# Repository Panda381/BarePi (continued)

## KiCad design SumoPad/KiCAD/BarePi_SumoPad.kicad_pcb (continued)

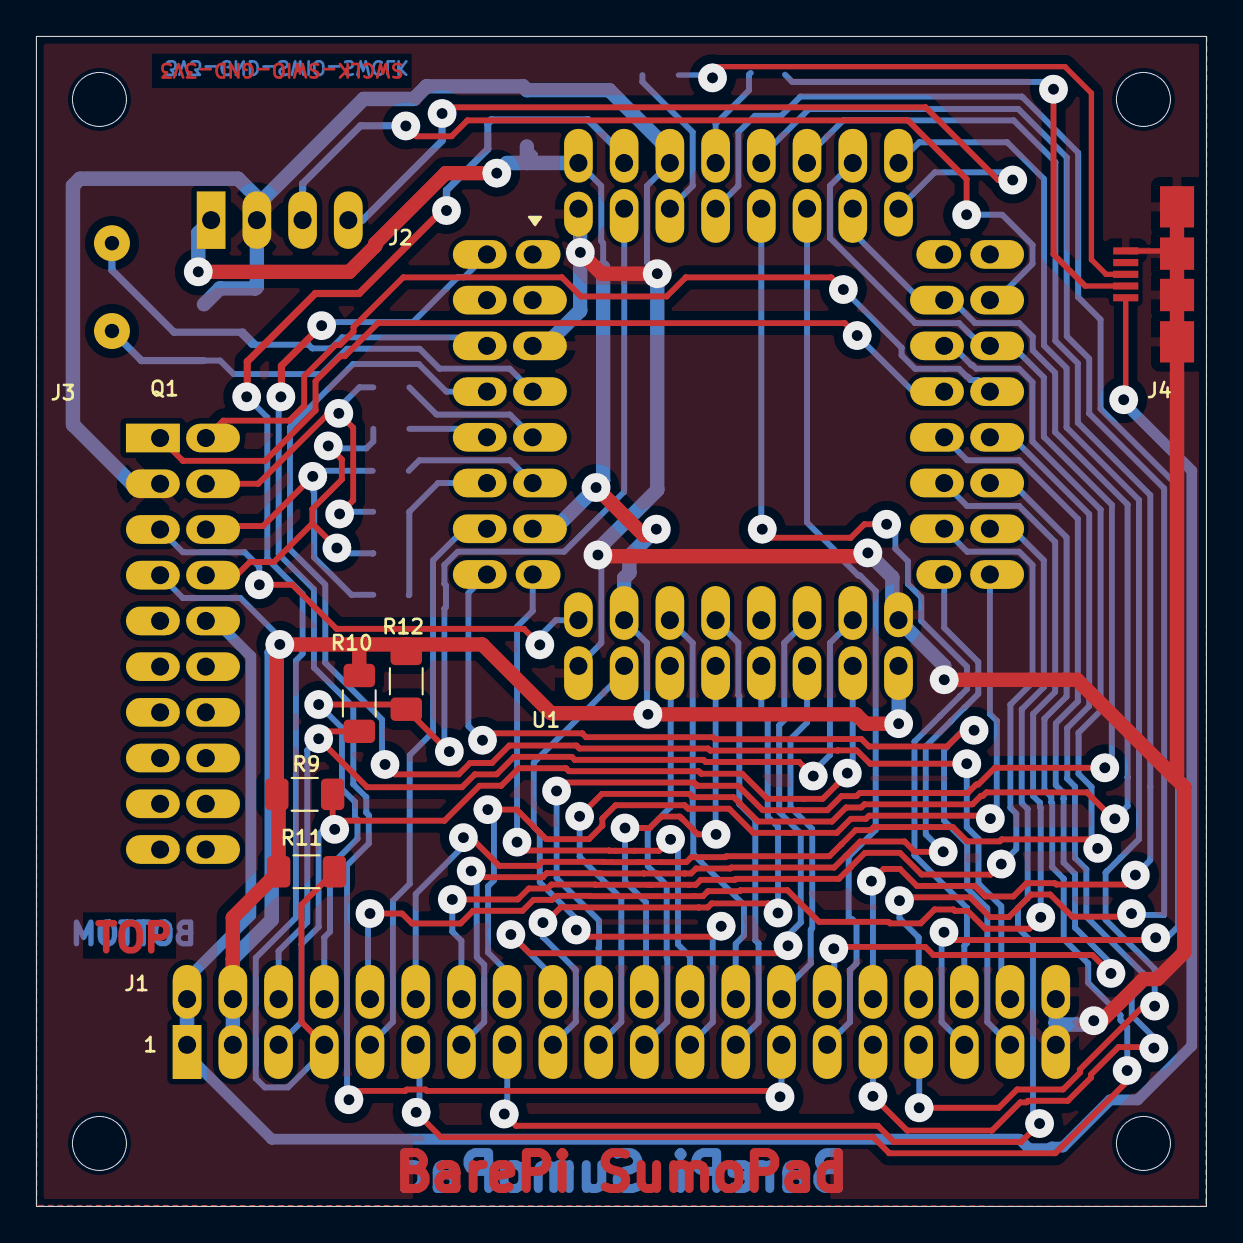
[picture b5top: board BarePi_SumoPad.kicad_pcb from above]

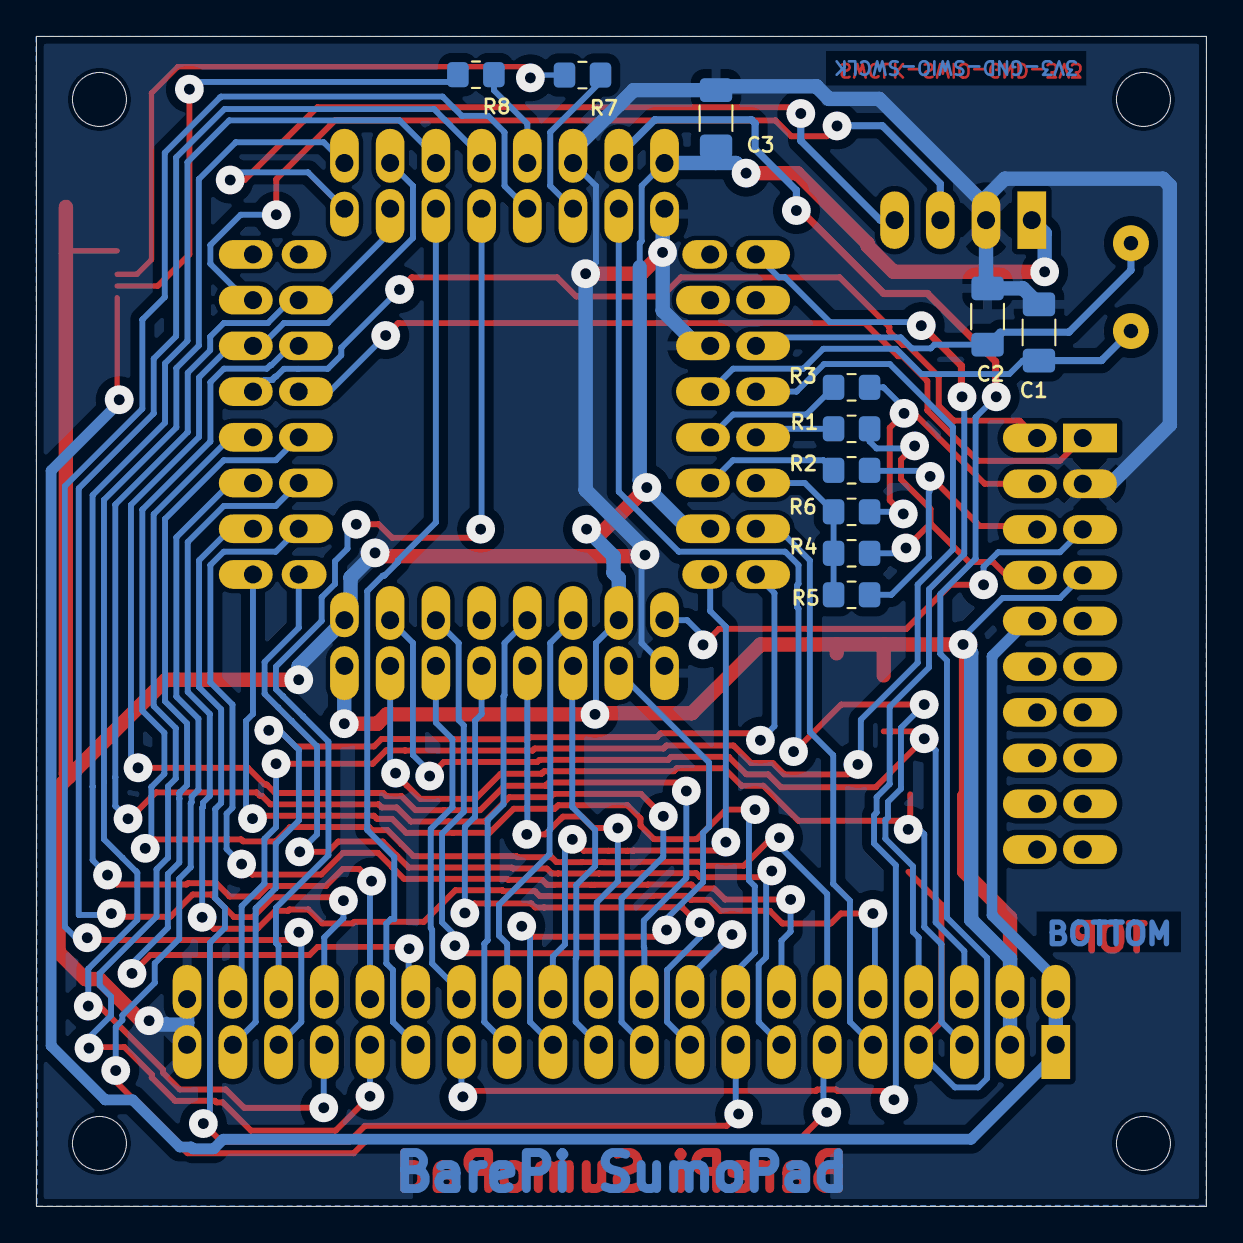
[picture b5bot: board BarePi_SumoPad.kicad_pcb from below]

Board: 2 copper layers, 65.0 x 65.0 mm, 21 parts (11 on the bottom side), 55 nets.

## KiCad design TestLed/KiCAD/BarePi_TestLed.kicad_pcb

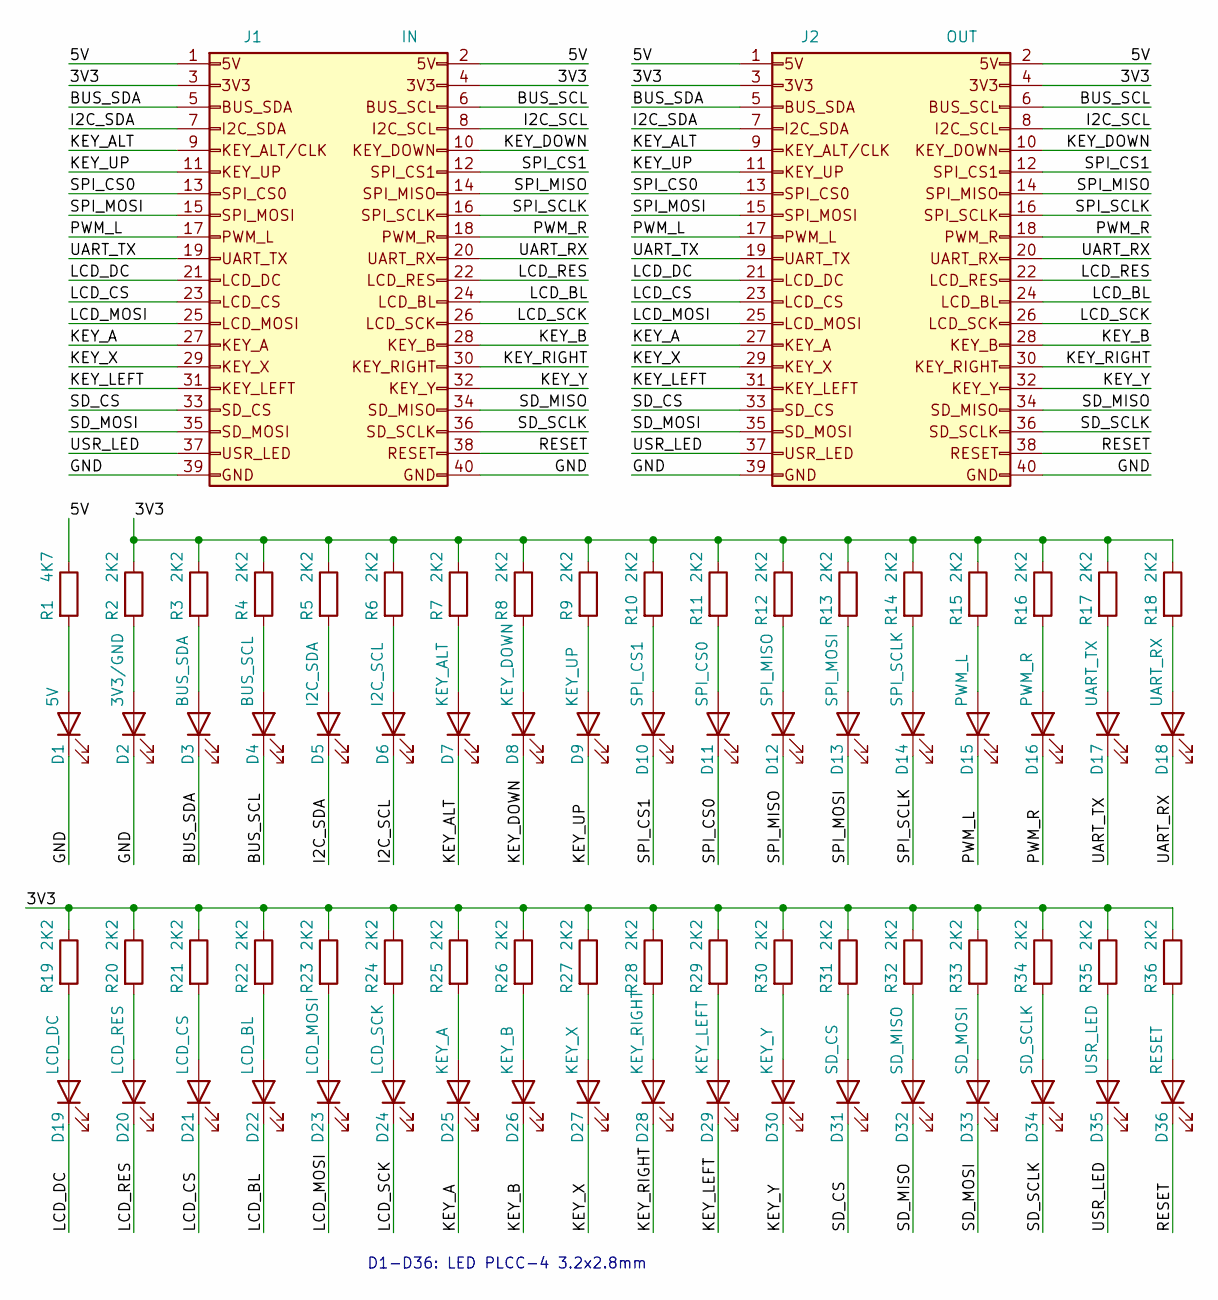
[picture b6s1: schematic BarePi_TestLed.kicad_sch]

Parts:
D1: 5V; Raspberry_LED_Avago_PLCC4_3.2x2.8mm_CW
D2: 3V3/GND; Raspberry_LED_Avago_PLCC4_3.2x2.8mm_CW
D3: BUS_SDA; Raspberry_LED_Avago_PLCC4_3.2x2.8mm_CW
D4: BUS_SCL; Raspberry_LED_Avago_PLCC4_3.2x2.8mm_CW
D5: I2C_SDA; Raspberry_LED_Avago_PLCC4_3.2x2.8mm_CW
D6: I2C_SCL; Raspberry_LED_Avago_PLCC4_3.2x2.8mm_CW
D7: KEY_ALT; Raspberry_LED_Avago_PLCC4_3.2x2.8mm_CW
D8: KEY_DOWN; Raspberry_LED_Avago_PLCC4_3.2x2.8mm_CW
D9: KEY_UP; Raspberry_LED_Avago_PLCC4_3.2x2.8mm_CW
D10: SPI_CS1; Raspberry_LED_Avago_PLCC4_3.2x2.8mm_CW
D11: SPI_CS0; Raspberry_LED_Avago_PLCC4_3.2x2.8mm_CW
D12: SPI_MISO; Raspberry_LED_Avago_PLCC4_3.2x2.8mm_CW
D13: SPI_MOSI; Raspberry_LED_Avago_PLCC4_3.2x2.8mm_CW
D14: SPI_SCLK; Raspberry_LED_Avago_PLCC4_3.2x2.8mm_CW
D15: PWM_L; Raspberry_LED_Avago_PLCC4_3.2x2.8mm_CW
D16: PWM_R; Raspberry_LED_Avago_PLCC4_3.2x2.8mm_CW
D17: UART_TX; Raspberry_LED_Avago_PLCC4_3.2x2.8mm_CW
D18: UART_RX; Raspberry_LED_Avago_PLCC4_3.2x2.8mm_CW
D19: LCD_DC; Raspberry_LED_Avago_PLCC4_3.2x2.8mm_CW
D20: LCD_RES; Raspberry_LED_Avago_PLCC4_3.2x2.8mm_CW
D21: LCD_CS; Raspberry_LED_Avago_PLCC4_3.2x2.8mm_CW
D22: LCD_BL; Raspberry_LED_Avago_PLCC4_3.2x2.8mm_CW
D23: LCD_MOSI; Raspberry_LED_Avago_PLCC4_3.2x2.8mm_CW
D24: LCD_SCK; Raspberry_LED_Avago_PLCC4_3.2x2.8mm_CW
D25: KEY_A; Raspberry_LED_Avago_PLCC4_3.2x2.8mm_CW
D26: KEY_B; Raspberry_LED_Avago_PLCC4_3.2x2.8mm_CW
D27: KEY_X; Raspberry_LED_Avago_PLCC4_3.2x2.8mm_CW
D28: KEY_RIGHT; Raspberry_LED_Avago_PLCC4_3.2x2.8mm_CW
D29: KEY_LEFT; Raspberry_LED_Avago_PLCC4_3.2x2.8mm_CW
D30: KEY_Y; Raspberry_LED_Avago_PLCC4_3.2x2.8mm_CW
D31: SD_CS; Raspberry_LED_Avago_PLCC4_3.2x2.8mm_CW
D32: SD_MISO; Raspberry_LED_Avago_PLCC4_3.2x2.8mm_CW
D33: SD_MOSI; Raspberry_LED_Avago_PLCC4_3.2x2.8mm_CW
D34: SD_SCLK; Raspberry_LED_Avago_PLCC4_3.2x2.8mm_CW
D35: USR_LED; Raspberry_LED_Avago_PLCC4_3.2x2.8mm_CW
D36: RESET; Raspberry_LED_Avago_PLCC4_3.2x2.8mm_CW
J1: IN; Raspberry_IN_PinHeader_2x20_P2.54mm_Horizontal
J2: OUT; Raspberry_OUT_PinSocket_2x20_P2.54mm_Horizontal
R1: 4K7; R_0805_2012Metric_Pad1.20x1.40mm_HandSolder
R2, R3, R4, R5, R6, R7, R8, R9, R10, R11, R12, R13, R14, R15, R16, R17, R18, R19, R20, R21, R22, R23, R24, R25, R26, R27, R28, R29, R30, R31, R32, R33, R34, R35, R36: 2K2; R_0805_2012Metric_Pad1.20x1.40mm_HandSolder

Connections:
/3V3: J1.3, J1.4, J2.3, J2.4, R2.1, R3.1, R4.1, R5.1, R6.1, R7.1, R8.1, R9.1, R10.1, R11.1, R12.1, R13.1, R14.1, R15.1, R16.1, R17.1, R18.1, R19.1, R20.1, R21.1, R22.1, R23.1, R24.1, R25.1, R26.1, R27.1, R28.1, R29.1, R30.1, R31.1, R32.1, R33.1, R34.1, R35.1, R36.1
/5V: J1.1, J1.2, J2.1, J2.2, R1.1
/BUS_SCL: D4.1 (K), J1.6, J2.6
/BUS_SDA: D3.1 (K), J1.5, J2.5
/GND: D1.1 (K), D2.1 (K), J1.39, J1.40, J2.39, J2.40
/I2C_SCL: D6.1 (K), J1.8, J2.8
/I2C_SDA: D5.1 (K), J1.7, J2.7
/KEY_A: D25.1 (K), J1.27, J2.27
/KEY_ALT: D7.1 (K), J1.9, J2.9
/KEY_B: D26.1 (K), J1.28, J2.28
/KEY_DOWN: D8.1 (K), J1.10, J2.10
/KEY_LEFT: D29.1 (K), J1.31, J2.31
/KEY_RIGHT: D28.1 (K), J1.30, J2.30
/KEY_UP: D9.1 (K), J1.11, J2.11
/KEY_X: D27.1 (K), J1.29, J2.29
/KEY_Y: D30.1 (K), J1.32, J2.32
/LCD_BL: D22.1 (K), J1.24, J2.24
/LCD_CS: D21.1 (K), J1.23, J2.23
/LCD_DC: D19.1 (K), J1.21, J2.21
/LCD_MOSI: D23.1 (K), J1.25, J2.25
/LCD_RES: D20.1 (K), J1.22, J2.22
/LCD_SCK: D24.1 (K), J1.26, J2.26
/PWM_L: D15.1 (K), J1.17, J2.17
/PWM_R: D16.1 (K), J1.18, J2.18
/RESET: D36.1 (K), J1.38, J2.38
/SD_CS: D31.1 (K), J1.33, J2.33
/SD_MISO: D32.1 (K), J1.34, J2.34
/SD_MOSI: D33.1 (K), J1.35, J2.35
/SD_SCLK: D34.1 (K), J1.36, J2.36
/SPI_CS0: D11.1 (K), J1.13, J2.13
/SPI_CS1: D10.1 (K), J1.12, J2.12
/SPI_MISO: D12.1 (K), J1.14, J2.14
/SPI_MOSI: D13.1 (K), J1.15, J2.15
/SPI_SCLK: D14.1 (K), J1.16, J2.16
/UART_RX: D18.1 (K), J1.20, J2.20
/UART_TX: D17.1 (K), J1.19, J2.19
/USR_LED: D35.1 (K), J1.37, J2.37
unnamed: D1.2 (A), R1.2
unnamed: D2.2 (A), R2.2
unnamed: D3.2 (A), R3.2
unnamed: D4.2 (A), R4.2
unnamed: D5.2 (A), R5.2
unnamed: D6.2 (A), R6.2
unnamed: D7.2 (A), R7.2
unnamed: D8.2 (A), R8.2
unnamed: D9.2 (A), R9.2
unnamed: D10.2 (A), R10.2
unnamed: D11.2 (A), R11.2
unnamed: D12.2 (A), R12.2
unnamed: D13.2 (A), R13.2
unnamed: D14.2 (A), R14.2
unnamed: D15.2 (A), R15.2
unnamed: D16.2 (A), R16.2
unnamed: D17.2 (A), R17.2
unnamed: D18.2 (A), R18.2
unnamed: D19.2 (A), R19.2
unnamed: D20.2 (A), R20.2
unnamed: D21.2 (A), R21.2
unnamed: D22.2 (A), R22.2
unnamed: D23.2 (A), R23.2
unnamed: D24.2 (A), R24.2
unnamed: D25.2 (A), R25.2
unnamed: D26.2 (A), R26.2
unnamed: D27.2 (A), R27.2
unnamed: D28.2 (A), R28.2
unnamed: D29.2 (A), R29.2
unnamed: D30.2 (A), R30.2
unnamed: D31.2 (A), R31.2
unnamed: D32.2 (A), R32.2
unnamed: D33.2 (A), R33.2
unnamed: D34.2 (A), R34.2
unnamed: D35.2 (A), R35.2
unnamed: D36.2 (A), R36.2

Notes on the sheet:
D1-D36: LED PLCC-4 3.2x2.8mm

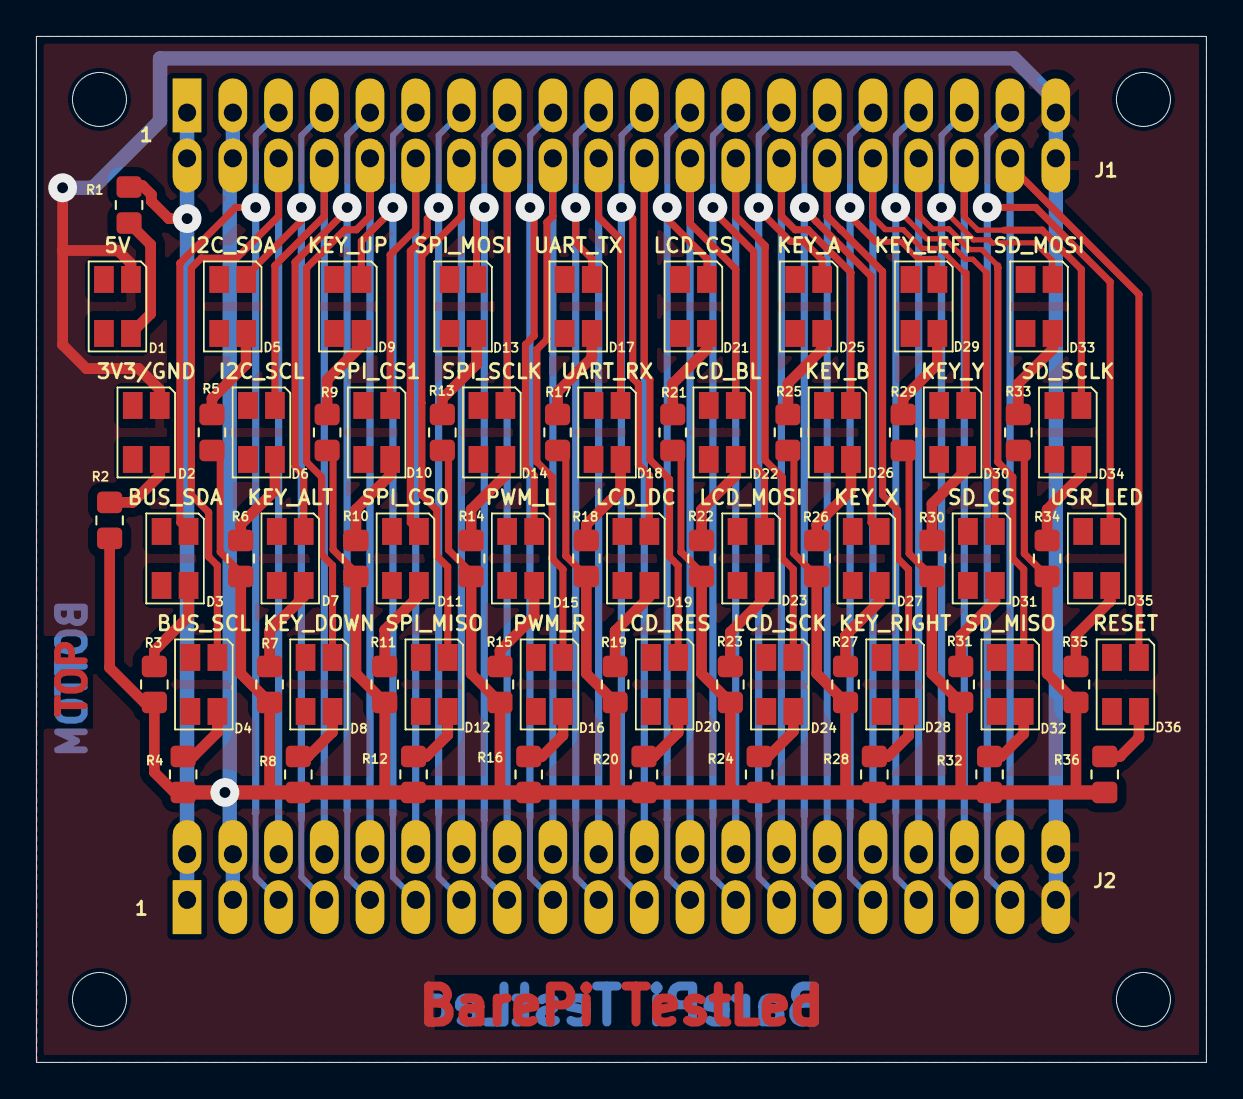
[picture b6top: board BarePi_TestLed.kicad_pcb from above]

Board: 2 copper layers, 65.0 x 57.0 mm, 74 parts (0 on the bottom side), 73 nets.

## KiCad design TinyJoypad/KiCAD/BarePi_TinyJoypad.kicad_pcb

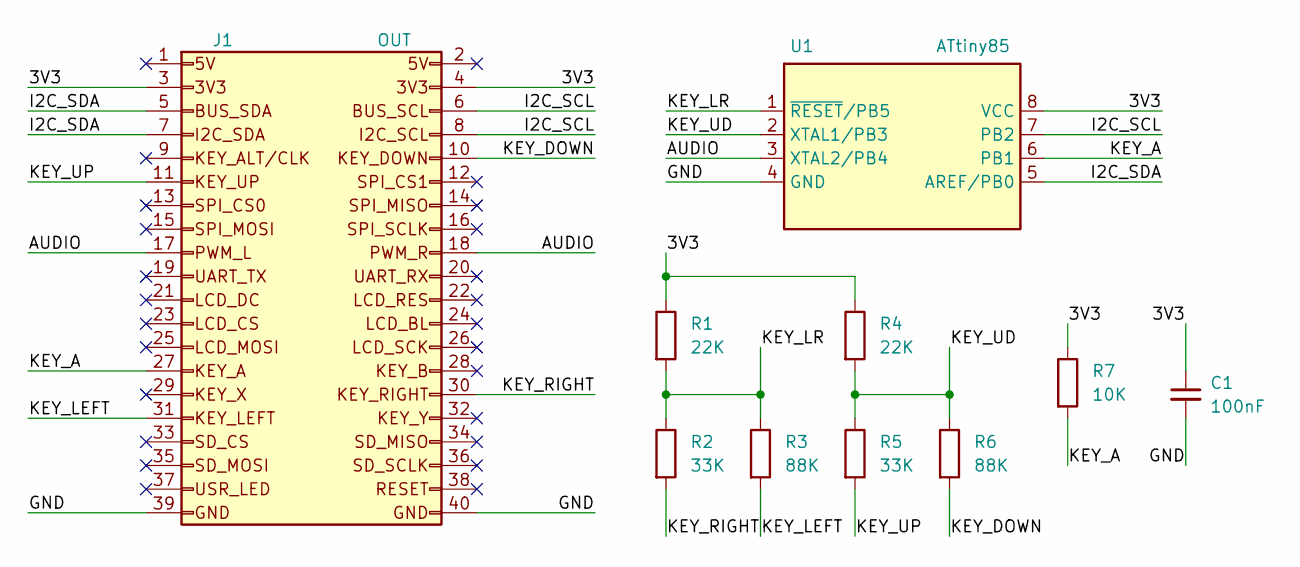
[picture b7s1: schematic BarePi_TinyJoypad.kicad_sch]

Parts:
C1: 100nF; C_1206_3216Metric_Pad1.33x1.80mm_HandSolder
J1: OUT; Raspberry_OUT_PinSocket_2x20_P2.54mm_Horizontal
R1, R4: 22K; R_1206_3216Metric_Pad1.30x1.75mm_HandSolder
R2, R5: 33K; R_1206_3216Metric_Pad1.30x1.75mm_HandSolder
R3, R6: 88K; R_1206_3216Metric_Pad1.30x1.75mm_HandSolder
R7: 10K; R_1206_3216Metric_Pad1.30x1.75mm_HandSolder
U1: ATtiny85; Raspberry_DIP-8_W7.62mm_Socket_LongPads

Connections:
/3V3: C1.1, J1.3, J1.4, R1.1, R4.1, R7.1, U1.8 (VCC)
/AUDIO: J1.17, J1.18, U1.3 (XTAL2/PB4)
/GND: C1.2, J1.39, J1.40, U1.4 (GND)
/I2C_SCL: J1.6, J1.8, U1.7 (PB2)
/I2C_SDA: J1.5, J1.7, U1.5 (AREF/PB0)
/KEY_A: J1.27, R7.2, U1.6 (PB1)
/KEY_DOWN: J1.10, R6.2
/KEY_LEFT: J1.31, R3.2
/KEY_LR: R1.2, R2.1, R3.1, U1.1 (~RESET/PB5)
/KEY_RIGHT: J1.30, R2.2
/KEY_UD: R4.2, R5.1, R6.1, U1.2 (XTAL1/PB3)
/KEY_UP: J1.11, R5.2

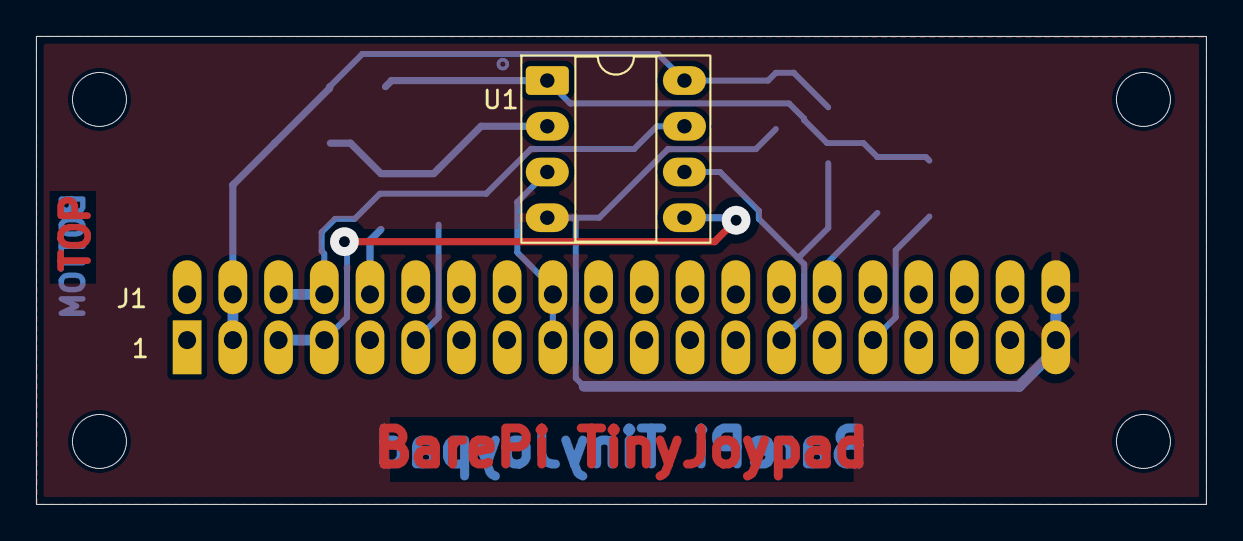
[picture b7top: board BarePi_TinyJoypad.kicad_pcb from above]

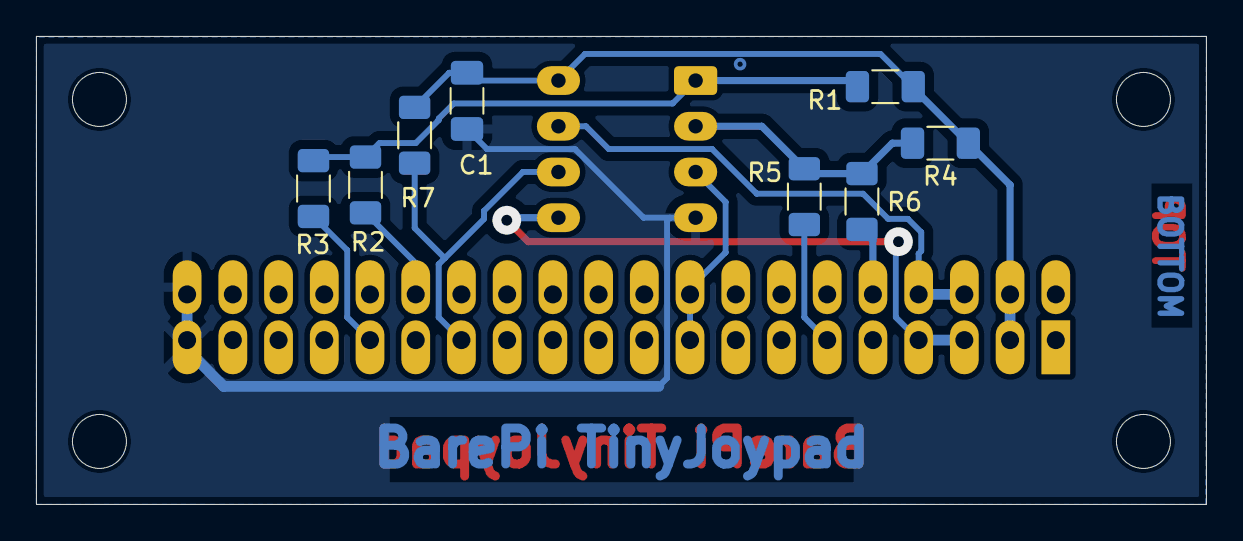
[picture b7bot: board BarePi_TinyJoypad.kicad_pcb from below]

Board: 2 copper layers, 65.0 x 26.0 mm, 10 parts (8 on the bottom side), 12 nets.
